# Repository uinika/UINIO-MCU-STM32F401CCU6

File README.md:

# UINIO-MCU-STM32F401CCU6 核心板

[**UINIO-MCU-STM32F401CCU6**](https://gitee.com/uinika/UINIO-MCU-STM32F401CCU6) 是一款基于 [**意法半导体**](https://www.st.com/zh/microcontrollers-microprocessors/stm32-32-bit-arm-cortex-mcus.html) **UFQFPN48** 封装的 **STM32F401CCU6** 微控制器的核心板电路设计，该微控制器基于 **ARM Cortex-M4** 内核架构，主频可以达到 `72MHz`，片上载有 `256KB` 容量的 Flash 存储器和 `64Kbytes` 的 SRAM 存储器，并且拥有 3 组 **USART** 和 3 组 **I²C** 接口，以及 4 组 **SPI** 接口与 `USB2.0` 全速控制器、12 位分辨率的 `ADC/DAC` 转换器，整体上属于高性价比、高性能的主控芯片产品。

> **注意**：相比较于采用 **ARM Cortex-M3** 内核架构的 **STM32F103C8T6** 等产品，使用 **ARM Cortex-M4** 内核的 **STM32F401CCU6** 携带有浮点计算单元（**FPU**，Float Point Unit），在处理数学计算时能够大幅度提升运算性能。

## 设计概要

1. 引出了意法半导体 **STM32F401CCU6** 型微控制器上面的全部 GPIO 引脚资源；
2. 单独提供有四线制的 **SWD** 下载接口，便于快速与 [UINIO-DAP-Link](http://uinio.com/Project/UINIO-DAP-Link) 建立连接；
3. 分别使用了 `8MHz` 与 `32.768KHz` 两枚贴片晶振作为系统外部时钟与实时时钟；
4. 板载 **BOOT0** 和 **BOOT1** 两枚启动配置按钮，以及一枚 **NRST** 复位按钮；
5. 模拟电源引脚 `VDDA` 使用了对 `100Mhz` 高频杂散信号存在 `1KΩ` 阻抗的**磁珠**进行单点接地；

## 启动配置

**UINIO-MCU-STM32F401CCU6** 通过板载的 `BOOT0` 和 `BOOT1` 两枚按钮来配置启动方式，默认情况下是从片上的 Flash 闪存进行启动，具体的配置信息可以参见下表：

| BOOT0 | BOOT1 | 启动方式                 |
| :---: | :---: | :----------------------- |
|  `0`  |  `X`  | 片上 Flash 闪存          |
|  `1`  |  `0`  | 系统存储器/ISP           |
|  `1`  |  `1`  | 片上 SRAM 静态随机存储器 |

## 参考技术文档

[UinIO.com 电子技术实验室](http://uinio.com/) 为 UINIO-MCU-STM32F401CCU6 开源项目提供了如下一系列技术参考资料：

1. [《基于 HAL 与 LL 的 UINIO-MCU-STM32F401 开发实践》](http://uinio.com/Embedded/STM32F401/)
2. [《ARM 调试工具 UINIO-DAP-Link 应用详解》](http://uinio.com/Project/UINIO-DAP-Link/)
3. [《BOM 交互式物料清单与 PCB 布线在线预览》](http://uinio.com/archives/BOM/UINIO-MCU-STM32F401CCU6.html)

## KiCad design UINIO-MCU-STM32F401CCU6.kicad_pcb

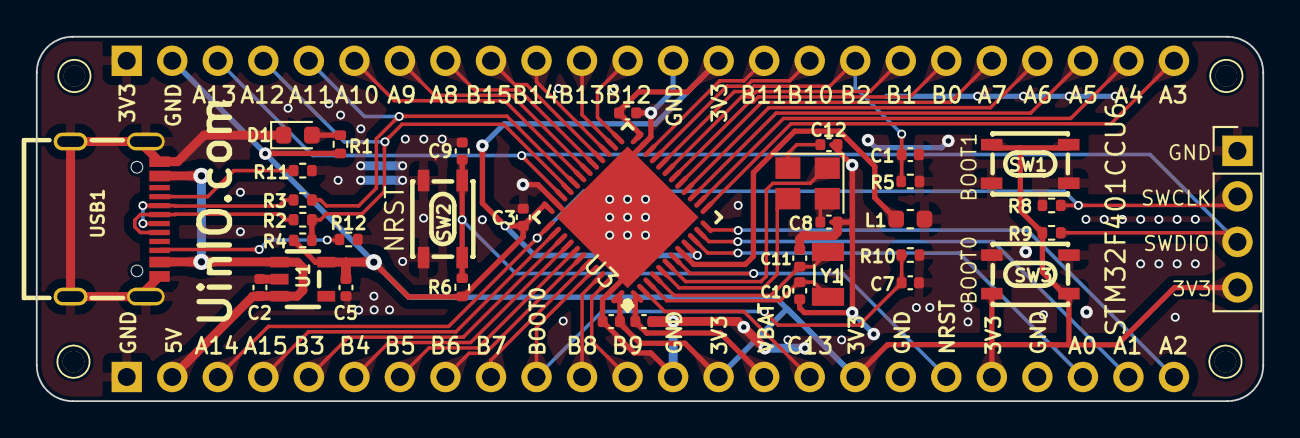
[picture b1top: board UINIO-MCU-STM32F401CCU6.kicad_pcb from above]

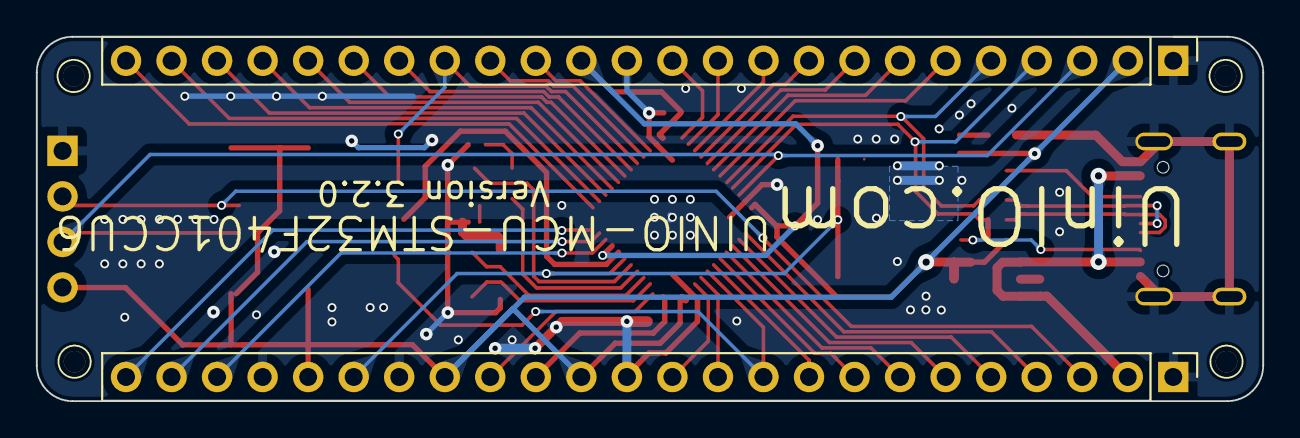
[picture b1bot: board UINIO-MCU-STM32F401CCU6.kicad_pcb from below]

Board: 2 copper layers, 68.4 x 20.3 mm, 41 parts (2 on the bottom side), 51 nets.

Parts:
C1, C3, C4, C6, C7, C9, C13: 0.1uF; C_0402_1005Metric
C2, C5: 1uF; C_0402_1005Metric
C8, C12: 22pF; C_0402_1005Metric
C10, C11: 10pF; C_0402_1005Metric
D1: LED_Red; LED_0603_1608Metric
HOLE**: Hole-1mm
HOLE**#2, HOLE**#3, HOLE**#4: Hole-1mm
J1, J2: Conn_01x24_Pin; PinHeader_1x24_P2.54mm_Vertical
J3: Conn_01x04_Pin; PinHeader_1x04_P2.54mm_Vertical
L1: 1KΩ 100Mhz; L_0603_1608Metric
R1: 2K; R_0402_1005Metric
R2, R3: 50R; R_0402_1005Metric
R4: 1.5K; R_0402_1005Metric
R5, R6, R8, R9, R10: 10K; R_0402_1005Metric
R11, R12: 5.1K; R_0402_1005Metric
SW1: BOOT1; KEY-SMD_4P-L4.2-W3.4-P2.15-LS4.7
SW2: NRST; KEY-SMD_4P-L4.2-W3.4-P2.15-LS4.7
SW3: BOOT0; KEY-SMD_4P-L4.2-W3.4-P2.15-LS4.7
U1: ME6211C33M5G-N; SOT-23-5_L3.0-W1.7-P0.95-LS2.8-BR
U3: STM32F401CCU6; UFQFPN-48_L7.0-W7.0-P0.50-TL-EP5.6
USB1: USB_Type_C_16Pin; USB-C-SMD_TYPEC-304J-BCP16
Y1: 32.768KHz; CRYSTAL-FC135-32.768
Y2: 8MHz; Crystal_SMD_3225-4Pin_3.2x2.5mm

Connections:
/BOOT0: C7.2, J2.10, R10.1, U3.44 (BOOT0)
/NRST: C9.1, J2.19, R6.2, SW2.1, SW2.2, U3.7 (NRST)
/PA0: J2.22, U3.10 (PA0_WAKEUP)
/PA1: J2.23, U3.11 (PA1)
/PA2: J2.24, U3.12 (PA2)
/PA3: J1.24, U3.13 (PA3)
/PA4: J1.23, U3.14 (PA4)
/PA5: J1.22, U3.15 (PA5)
/PA6: J1.21, U3.16 (PA6)
/PA7: J1.20, U3.17 (PA7)
/PA8: J1.8, U3.29 (PA8)
/PA9: J1.7, U3.30 (PA9)
/PA10: J1.6, U3.31 (PA10)
/PA13/SWDIO: J1.3, J3.3, R9.1, U3.34 (PA13)
/PA14/SWCLK: J2.3, J3.2, R8.2, U3.37 (PA14)
/PA15: J2.4, U3.38 (PA15)
/PB0: J1.19, U3.18 (PB0)
/PB1: J1.18, U3.19 (PB1)
/PB2/BOOT1: C1.2, J1.17, R5.1, U3.20 (PB2)
/PB3: J2.5, U3.39 (PB3)
/PB4: J2.6, U3.40 (PB4)
/PB5: J2.7, U3.41 (PB5)
/PB6: J2.8, U3.42 (PB6)
/PB7: J2.9, U3.43 (PB7)
/PB8: J2.11, U3.45 (PB8)
/PB9: J2.12, U3.46 (PB9)
/PB10: J1.16, U3.21 (PB10)
/PB11: J1.15, U3.22 (PB11)
/PB12: J1.12, U3.25 (PB12)
/PB13: J1.11, U3.26 (PB13)
/PB14: J1.10, U3.27 (PB14)
/PB15: J1.9, U3.28 (PB15)
/PC13: J2.16, U3.2 (PC13_TAMPER_RTC)
/USB_Data+: R2.1, USB1.A6 (DP1), USB1.B6 (DP2)
/USB_Data-: R3.1, USB1.A7 (DN1), USB1.B7 (DN2)
/USB_PA+: J1.4, R2.2, R4.2, U3.33 (PA12)
/USB_PA-: J1.5, R3.2, U3.32 (PA11)
/VBAT: C13.1, J2.15, U3.1 (VBAT)
/VDD_3.3V: C3.2, C4.2, C5.2, C6.2, J1.2, J1.14, J2.14, J2.17, J2.20, J3.4, R1.2, R4.1, R6.1, R9.2, SW1.3, SW1.4, SW3.3, SW3.4, U1.5 (Vout), U3.9 (VDDA), U3.24 (VDD_1), U3.36 (VDD_2), U3.48 (VDD_3)
/VDD_5V: C2.2, J2.2, U1.1 (Vin), U1.3 (CE), USB1.A4B9 (VBUS), USB1.B4A9 (VBUS)
GND: C1.1, C2.1, C3.1, C4.1, C5.1, C6.1, C7.1, C8.1, C9.2, C10.1, C11.1, C12.1, C13.2, D1.1 (K), J1.1, J1.13, J2.1, J2.13, J2.18, J2.21, J3.1, L1.1, R5.2, R8.1, R10.2, R11.2, R12.2, SW1.1, SW1.2, SW2.3, SW2.4, SW3.1, SW3.2, U1.2 (Vss), U3.23 (VSS_1), U3.35 (VSS_2), U3.47 (VSS_3), U3.49 (PAD), USB1.13 (GND), USB1.14 (GND), USB1.15 (GND), USB1.16 (GND), USB1.A1B12 (GND), USB1.B1A12 (GND)
unnamed: C8.2, Y2.4
unnamed: C12.2, Y2.2
unnamed: D1.2 (A), R1.1
unnamed: C10.2, U3.3 (PC14_OSC32_IN), Y1.2 (GND)
unnamed: C11.2, U3.4 (PC15_OSC32_OUT), Y1.1
unnamed: U3.5 (PD0_OSC_IN), Y2.3
unnamed: U3.6 (PD1_OSC_OUT), Y2.1
unnamed: L1.2, U3.8 (VSSA)
unnamed: R11.1, USB1.A5 (CC1)
unnamed: R12.1, USB1.B5 (CC2)

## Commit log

2024-02-06 Release UINIO-MCU-STM32F401CCU6 version 3.0.0.
2024-02-07 Update references folder.
2024-02-07 Update README.md.
2024-04-12 Release UINIO-MCU-STM32F401CCU6 version 3.1.0.
2024-04-13 Release UINIO-MCU-STM32F401CCU6 version 3.2.0.
